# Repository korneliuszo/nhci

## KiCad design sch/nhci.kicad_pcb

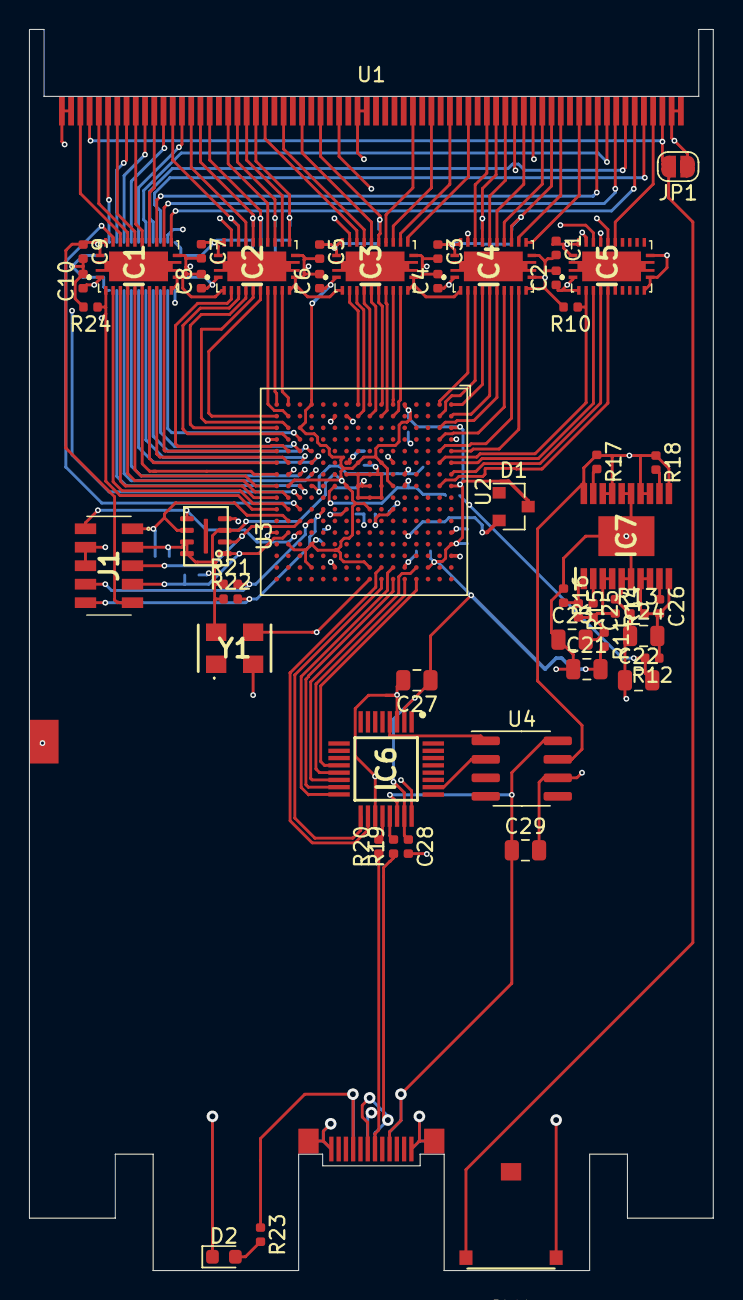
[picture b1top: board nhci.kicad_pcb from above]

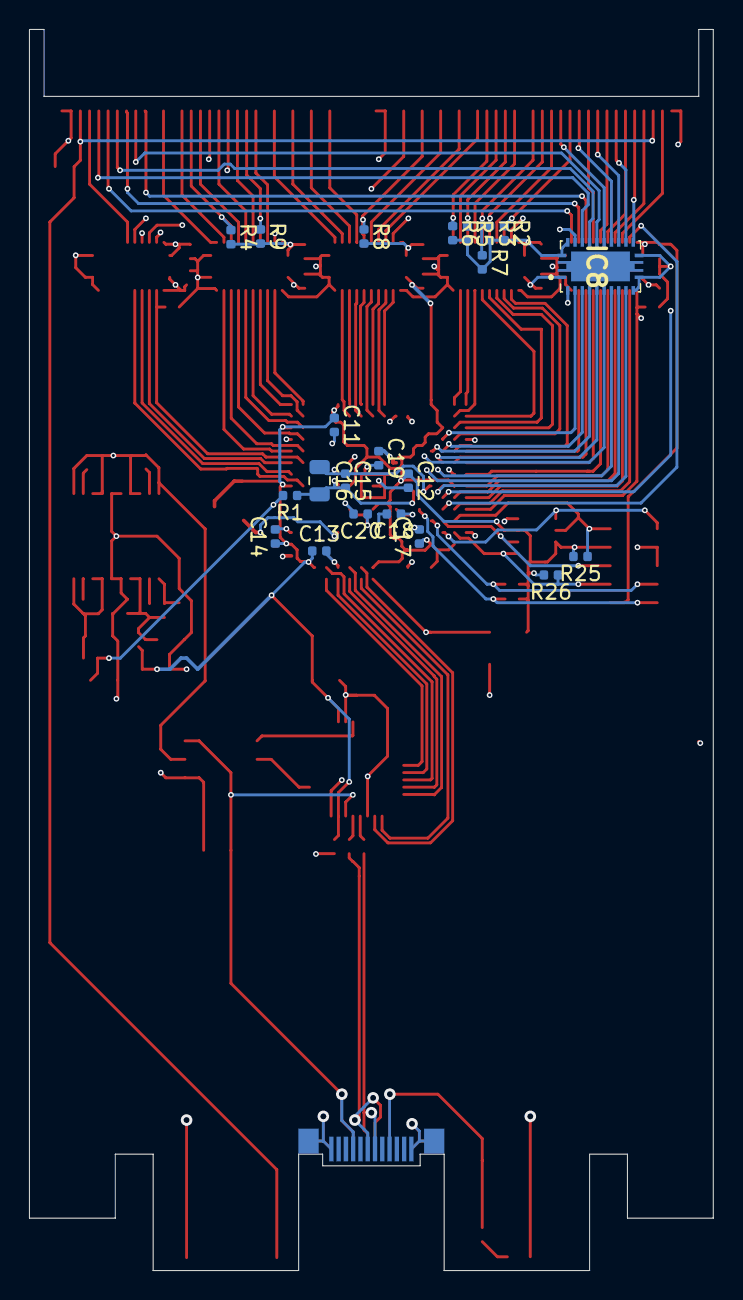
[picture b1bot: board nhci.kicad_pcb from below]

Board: 4 copper layers, 47.0 x 85.3 mm, 73 parts (22 on the bottom side), 128 nets.

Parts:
C1, C2, C3, C4, C5, C6, C7, C8, C9, C10, C11, C12, C13, C14, C15, C17, C28: 100nF; C_0402_1005Metric
C16, C21, C22, C23: 10uF; C_0805_2012Metric
C18, C19, C20, C25, C26: 10nF; C_0402_1005Metric
C24, C29: 4.7uF; C_0805_2012Metric
C27: 1uF; C_0805_2012Metric
D1: BAT54S; SOT-23
D2: LED; LED_0603_1608Metric
IC1, IC2, IC3, IC4, IC5, IC8: 74LVC8T245RHLRG4
IC6: MAX3421EEHJ+; QFP50P700X700X120-32N
IC7: LT3030IFE#TRPBF; SOP65P640X120-21N
J1: CLP-105-02-F-D; CLP-105-02-XXX-D
JP1: SolderJumper_2_Bridged; SolderJumper-2_P1.3mm_Open_RoundedPad1.0x1.5mm
R1, R13, R14: 100; R_0402_1005Metric
R2, R3, R4, R5, R6, R7, R8, R10, R21, R22, R24, R25, R26: 10k; R_0402_1005Metric
R9: 100k; R_0402_1005Metric
R11, R12: 0.1; R_0402_1005Metric
R15: 357k; R_0402_1005Metric
R16: 210k; R_0402_1005Metric
R17, R18: 1M; R_0402_1005Metric
R19, R20: 33; R_0402_1005Metric
R23: 1k; R_0402_1005Metric
SW1: SW_Push_Open; KSM1131
U1: PCMCIA_BOARD; PCMCIA_CARD
U2: iCE40-HX8K-CT256; BGA-256_14.0x14.0mm_Layout16x16_P0.8mm_Ball0.45mm_Pad0.32mm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
U3: N25Q032A13EF440F
U4: LM3526M-H; SOIC-8_3.9x4.9mm_P1.27mm
Y1: ECS-5032MV-120-BM-TR; ECS5032MV120BMTR

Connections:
12MHz: IC6.24, U2.H16, Y1.3
+1V2: C18.1, C19.1, C20.1, C22.2, R1.2, R12.2, U2.A14, U2.F6, U2.F10, U2.K6, U2.K10, U2.L2
+3V3: C2.1, C4.1, C6.1, C8.1, C10.1, C11.1, C12.1, C13.1, C14.1, C17.1, C21.2, C27.1, C28.1, D1.3, IC1.1, IC2.1, IC3.1, IC4.1, IC5.1, IC5.2, IC6.2, IC6.23, IC8.1, J1.3, R11.2, R21.1, R22.1, R25.2, R26.2, U2.A3, U2.A8, U2.A13, U2.C15, U2.E1, U2.F8, U2.G6, U2.H10, U2.H15, U2.J6, U2.K8, U2.N1, U2.N13, U2.N15, U2.P3, U2.R8, U2.R13, U3.3, U3.7, U3.8, Y1.4
+5V: C1.1, C3.1, C5.1, C7.1, C9.1, IC1.23, IC1.24, IC2.23, IC2.24, IC3.23, IC3.24, IC4.23, IC4.24, IC5.23, IC5.24, IC7.11, IC7.13, IC7.14, IC7.17, IC7.18, IC7.20, IC8.23, IC8.24, J1.9, R2.2, R3.2, R4.2, R5.2, R6.2, R7.2, R8.2, R9.2, R17.1, R18.1, U1.17, U1.51, U4.7
/P_A0: IC4.14, U1.29
/P_A1: IC4.15, U1.28
/P_A2: IC4.17, U1.27
/P_A3: IC4.18, U1.26
/P_A4: IC4.19, U1.25
/P_A5: IC4.21, U1.24
/P_A6: IC3.14, U1.23
/P_A7: IC3.15, U1.22
/P_A8: IC3.21, U1.12
/P_A9: IC2.15, U1.11
/P_A10: IC2.20, U1.8
/P_A11: IC2.17, U1.10
/P_A12: IC3.16, U1.21
/P_A13: IC3.20, U1.13
/P_A14: IC3.19, U1.14
/P_A15: IC3.17, U1.20
/P_CE1: IC2.21, R2.1, U1.7
/P_CE2: IC2.19, R3.1, U1.42
/P_D0: IC1.16, U1.30
/P_D1: IC1.15, U1.31
/P_D2: IC1.14, U1.32
/P_D3: IC1.21, U1.2
/P_D4: IC1.20, U1.3
/P_D5: IC1.19, U1.4
/P_D6: IC1.18, U1.5
/P_D7: IC1.17, U1.6
/P_D8: IC8.19, U1.64
/P_D9: IC8.20, U1.65
/P_D10: IC8.21, U1.66
/P_D11: IC8.14, U1.37
/P_D12: IC8.15, U1.38
/P_D13: IC8.16, U1.39
/P_D14: IC8.17, U1.40
/P_D15: IC8.18, U1.41
/P_INPACK: IC5.19, U1.60
/P_IORD: IC2.16, R5.1, U1.44
/P_IOWR: IC2.14, R6.1, U1.45
/P_OE: IC2.18, R7.1, U1.9
/P_READY: IC5.21, U1.16
/P_REG: IC4.16, R4.1, U1.61
/P_RESET: IC4.20, R9.1, U1.58
/P_WAIT: IC5.20, U1.59
/P_WE: IC3.18, R8.1, U1.15
/P_WP: IC5.18, U1.33
CDONE: J1.10, R22.2, U2.M10
CRESET: J1.8, R21.2, U2.N11
F_A0: IC4.10, U2.A5
F_A1: IC4.9, U2.B5
F_A2: IC4.7, U2.B3
F_A3: IC4.6, U2.A2
F_A4: IC4.5, U2.A1
F_A5: IC4.3, U2.B1
F_A6: IC3.10, U2.F2
F_A7: IC3.9, U2.F1
F_A8: IC3.3, U2.J1
F_A9: IC2.9, U2.T1
F_A10: IC2.4, U2.R4
F_A11: IC2.7, U2.T2
F_A12: IC3.8, U2.G2
F_A13: IC3.4, U2.J2
F_A14: IC3.5, U2.H1
F_A15: IC3.7, U2.G1
F_CE1: IC2.3, U2.R5
F_CE1O: IC1.22, U2.P10
F_CE2: IC2.5, U2.T3
F_CE2O: IC8.22, U2.P9
F_D0: IC1.8, U2.T6
F_D1: IC1.9, U2.R6
F_D2: IC1.10, U2.T5
F_D3: IC1.3, U2.R10
F_D4: IC1.4, U2.T9
F_D5: IC1.5, U2.R9
F_D6: IC1.6, U2.T8
F_D7: IC1.7, U2.T7
F_D8: IC8.5, U2.N5
F_D9: IC8.4, U2.P5
F_D10: IC8.3, U2.P4
F_D11: IC8.10, U2.P8
F_D12: IC8.9, U2.N7
F_D13: IC8.8, U2.P7
F_D14: IC8.7, U2.N6
F_D15: IC8.6, U2.P6
F_DDIR: IC1.2, IC8.2, R24.1, U2.T10
F_INPACK: IC5.5, U2.A7
F_IORD: IC2.8, U2.R2
F_IOWR: IC2.10, U2.R1
F_OE: IC2.6, U2.R3
F_READY: IC5.3, R10.1, U2.B6
F_REG: IC4.8, U2.B4
F_RESET: IC4.4, U2.B2
F_WAIT: IC5.4, U2.A6
F_WE: IC3.6, U2.H2
F_WP: IC5.6, U2.B8
GND: C1.2, C2.2, C3.2, C4.2, C5.2, C6.2, C7.2, C8.2, C9.2, C10.2, C11.2, C12.2, C13.2, C14.2, C17.2, C18.2, C19.2, C20.2, C21.1, C22.1, C23.1, C24.1, C27.2, C28.2, C29.2, D2.1, IC1.11, IC1.12, IC1.13, IC2.2, IC2.11, IC2.12, IC2.13, IC2.22, IC3.2, IC3.11, IC3.12, IC3.13, IC3.22, IC4.2, IC4.11, IC4.12, IC4.13, IC4.22, IC5.11, IC5.12, IC5.13, IC5.22, IC6.3, IC6.19, IC7.5, IC7.6, IC7.15, IC7.16, IC7.21, IC8.11, IC8.12, IC8.13, J1.4, J1.6, JP1.1, R10.2, R13.1, R14.1, R16.1, R24.2, SW1.1, U1.1, U1.34, U1.35, U1.68, U1.A1, U1.A12, U1.B1, U1.B12, U1.GCLIP, U1.SH, U1.SH2, U1.SH3, U1.SH4, U2.A4, U2.A12, U2.E15, U2.G7, U2.G8, U2.G9, U2.H7, U2.H8, U2.H9, U2.J7, U2.J8, U2.J9, U2.K2, U2.K7, U2.L15, U2.R7, U2.T4, U2.T12, U3.4, U4.6, Y1.2
unnamed: C15.1, C16.1, U2.E7, U2.N8
unnamed: C15.2, C16.2, R1.1, U2.E8, U2.L8
unnamed: C23.2, C25.2, IC7.3, IC7.4, R11.1, R14.2, R15.2
unnamed: C24.2, C26.2, IC7.7, IC7.8, IC7.10, R12.1, R13.2
unnamed: C25.1, IC7.2
unnamed: C26.1, IC7.9
unnamed: C29.1, IC6.22, R23.1, U1.A4, U1.A9, U1.B4, U1.B9, U4.8
unnamed: D1.2, U2.E12
unnamed: D2.2, R23.2
unnamed: IC6.4, U4.1
unnamed: IC6.20, R20.2
unnamed: IC6.21, R19.2
unnamed: IC6.26, U4.2
unnamed: IC7.1, R15.1, R16.2
unnamed: IC7.12, R18.2
unnamed: IC7.19, R17.2
unnamed: J1.1, R25.1, U2.R11, U3.6
unnamed: J1.2, U2.P12, U3.5
unnamed: J1.5, U2.P11, U3.2
unnamed: J1.7, R26.1, U2.R12, U3.1
unnamed: JP1.2, SW1.2, U1.36, U1.67
unnamed: R19.1, U1.A6, U1.B6
unnamed: R20.1, U1.A7, U1.B7
U_GPX: IC6.17, U2.G16
U_INT: IC6.18, U2.G15
U_MISO: IC6.15, U2.F16
U_MOSI: IC6.16, U2.F15
U_RES: IC6.12, U2.D16
U_SCLK: IC6.13, U2.E16
U_SS: IC6.14, U2.D15

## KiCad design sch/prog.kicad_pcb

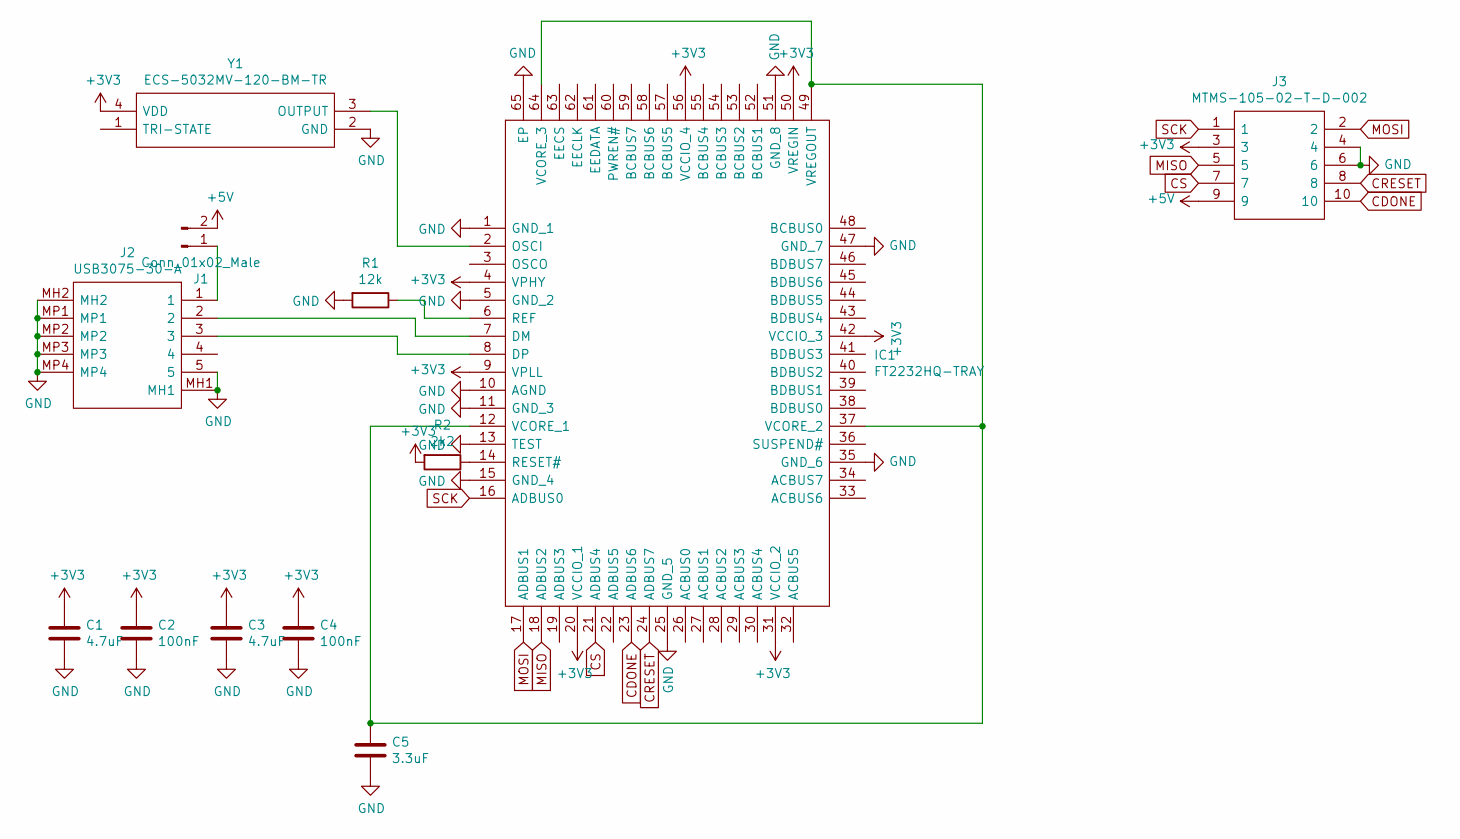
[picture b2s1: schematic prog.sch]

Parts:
C1, C3: 4.7uF; C_0805_2012Metric
C2, C4: 100nF; C_0805_2012Metric
C5: 3.3uF; C_0805_2012Metric
IC1: FT2232HQ-TRAY; QFN50P900X900X90-65N-D; Manufacturer_Part_Number FT2232HQ-TRAY; Mouser Part Number 895-FT2232HQ-TRAY
J1: Conn_01x02_Male; PinHeader_1x02_P2.54mm_Horizontal
J2: USB3075-30-A; USB307530A; Manufacturer_Part_Number USB3075-30-A
J3: MTMS-105-02-T-D-002; MTMS10502TD002; Manufacturer_Part_Number MTMS-105-02-T-D-002; Mouser Part Number 200-MTMS10502TD002
R1: 12k; R_0805_2012Metric
R2: 2k2; R_0805_2012Metric
Y1: ECS-5032MV-120-BM-TR; ECS5032MV120BMTR; Manufacturer_Part_Number ECS-5032MV-120-BM-TR; Mouser Part Number 520-5032MV-120-BMT

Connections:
+3V3: C1.1, C2.1, C3.1, C4.1, IC1.4 (VPHY), IC1.9 (VPLL), IC1.20 (VCCIO_1), IC1.31 (VCCIO_2), IC1.42 (VCCIO_3), IC1.50 (VREGIN), IC1.56 (VCCIO_4), J3.3, R2.2, Y1.4 (VDD)
+5V: J1.2, J3.9
CDONE: IC1.23 (ADBUS6), J3.10
CRESET: IC1.24 (ADBUS7), J3.8
CS: IC1.21 (ADBUS4), J3.7
GND: C1.2, C2.2, C3.2, C4.2, C5.2, IC1.1 (GND_1), IC1.5 (GND_2), IC1.10 (AGND), IC1.11 (GND_3), IC1.13 (TEST), IC1.15 (GND_4), IC1.25 (GND_5), IC1.35 (GND_6), IC1.47 (GND_7), IC1.51 (GND_8), IC1.65 (EP), J2.5, J2.MH1, J2.MH2, J2.MP1, J2.MP2, J2.MP3, J2.MP4, J3.4, J3.6, R1.2, Y1.2 (GND)
MISO: IC1.18 (ADBUS2), J3.5
MOSI: IC1.17 (ADBUS1), J3.2
unnamed: C5.1, IC1.12 (VCORE_1), IC1.37 (VCORE_2), IC1.49 (VREGOUT), IC1.64 (VCORE_3)
unnamed: IC1.2 (OSCI), Y1.3 (OUTPUT)
unnamed: IC1.6 (REF), R1.1
unnamed: IC1.7 (DM), J2.2
unnamed: IC1.8 (DP), J2.3
unnamed: IC1.14 (RESET#), R2.1
unnamed: J1.1, J2.1
SCK: IC1.16 (ADBUS0), J3.1

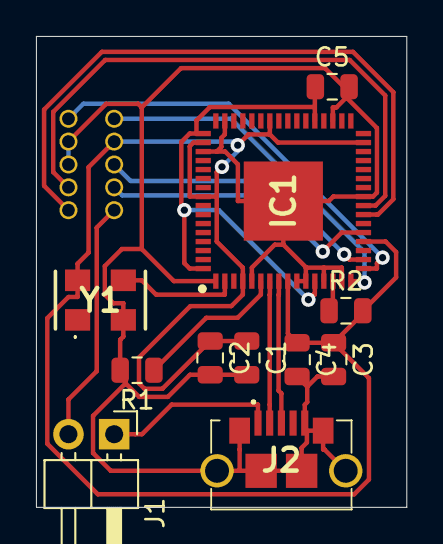
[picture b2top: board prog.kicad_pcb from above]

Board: 2 copper layers, 20.6 x 26.2 mm, 12 parts (1 on the bottom side), 16 nets.

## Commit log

2021-04-19 Stub windows driver
2021-04-20 Add libraries
2021-04-20 Add N25Q032A13EF440F
2021-04-20 Add switch
2021-04-21 Add PCMCIA footprint (TODO: USB connector)
2021-04-21 Add LM3526M-H symbol
2021-04-22 Add nonfinished schematic
2021-04-22 Add pullup resistors
2021-04-22 Add LT3030 library
2021-04-22 Add voltage regulator
2021-04-22 Add usb controller
2021-04-22 Add solder jumper for non development board
2021-04-22 Route forgotten
2021-04-22 Add programming connector
2021-04-22 Add missing route
2021-04-22 Add start programmer
2021-04-22 Autoroute
2021-04-22 Add proper value of resistors
2021-04-22 Add power led
2021-04-22 Add pulldown resistor so when FPGA boots no load on data bus
2021-04-23 Add Connector
2021-04-23 Add eaten resistor (move between machines)
2021-04-23 Replace diode
2021-04-23 VCC is 1V2 not 3V3
2021-04-23 Remove backup
2021-04-23 gitignore backups
2021-04-23 Add recommended SPI pullups
2021-04-23 Add edge cuts
2021-04-23 Add gerbers (commit to manufacture?)
2021-04-23 Add stub for fpga software
2021-04-26 Move common variables to COMMON_TOP
2021-04-26 First verilator usage (apio and system needed)
2021-04-26 Add clock constraints
2021-04-26 We use it as reg for now
2021-04-27 CXXRTL simulation - split between ic.v (for synthesis) and top.v
2021-04-27 Forgot put ic.v in previous commit
2021-04-27 Add proper pcf
2021-04-28 update ice40-cmake
2021-04-28 Add stub of simulation
2021-04-28 Simulate readattr
2021-04-28 Remove warnings
2021-04-28 Add configuration tuple
2021-04-28 Proper define
2021-04-29 Allow older CMake
2021-04-29 Small fixes
2021-04-29 Implement SET_ATTR_MEMORY
2021-04-29 Add configuration register
2021-04-29 Change behaviour to WE edge latch
2021-05-04 Spi slave simulator
2021-05-05 Proper direction
2021-05-05 Faster clock
2021-05-05 Support io interface
2021-05-05 Add spi module
2021-05-06 Fix clock
2021-05-06 FF instead of Latch
2021-05-06 Synchronize 2 clocks for no race with posedge IOWR
2021-05-06 Proper silkscreen and distances from pads
2021-05-06 PCB V1.1
2021-05-11 Latch A[1]
2021-05-13 Add u_res signal
2021-05-24 Disable optimizations
2021-05-24 Add pullup to INT from usb controller
2021-05-24 Rewire reset
2021-05-24 Fix simulation
2021-05-24 Fix spi
2021-05-24 Add test.py for switching on power to usb
2021-05-24 su: ice40-cmake
2021-09-21 V2.0 board
